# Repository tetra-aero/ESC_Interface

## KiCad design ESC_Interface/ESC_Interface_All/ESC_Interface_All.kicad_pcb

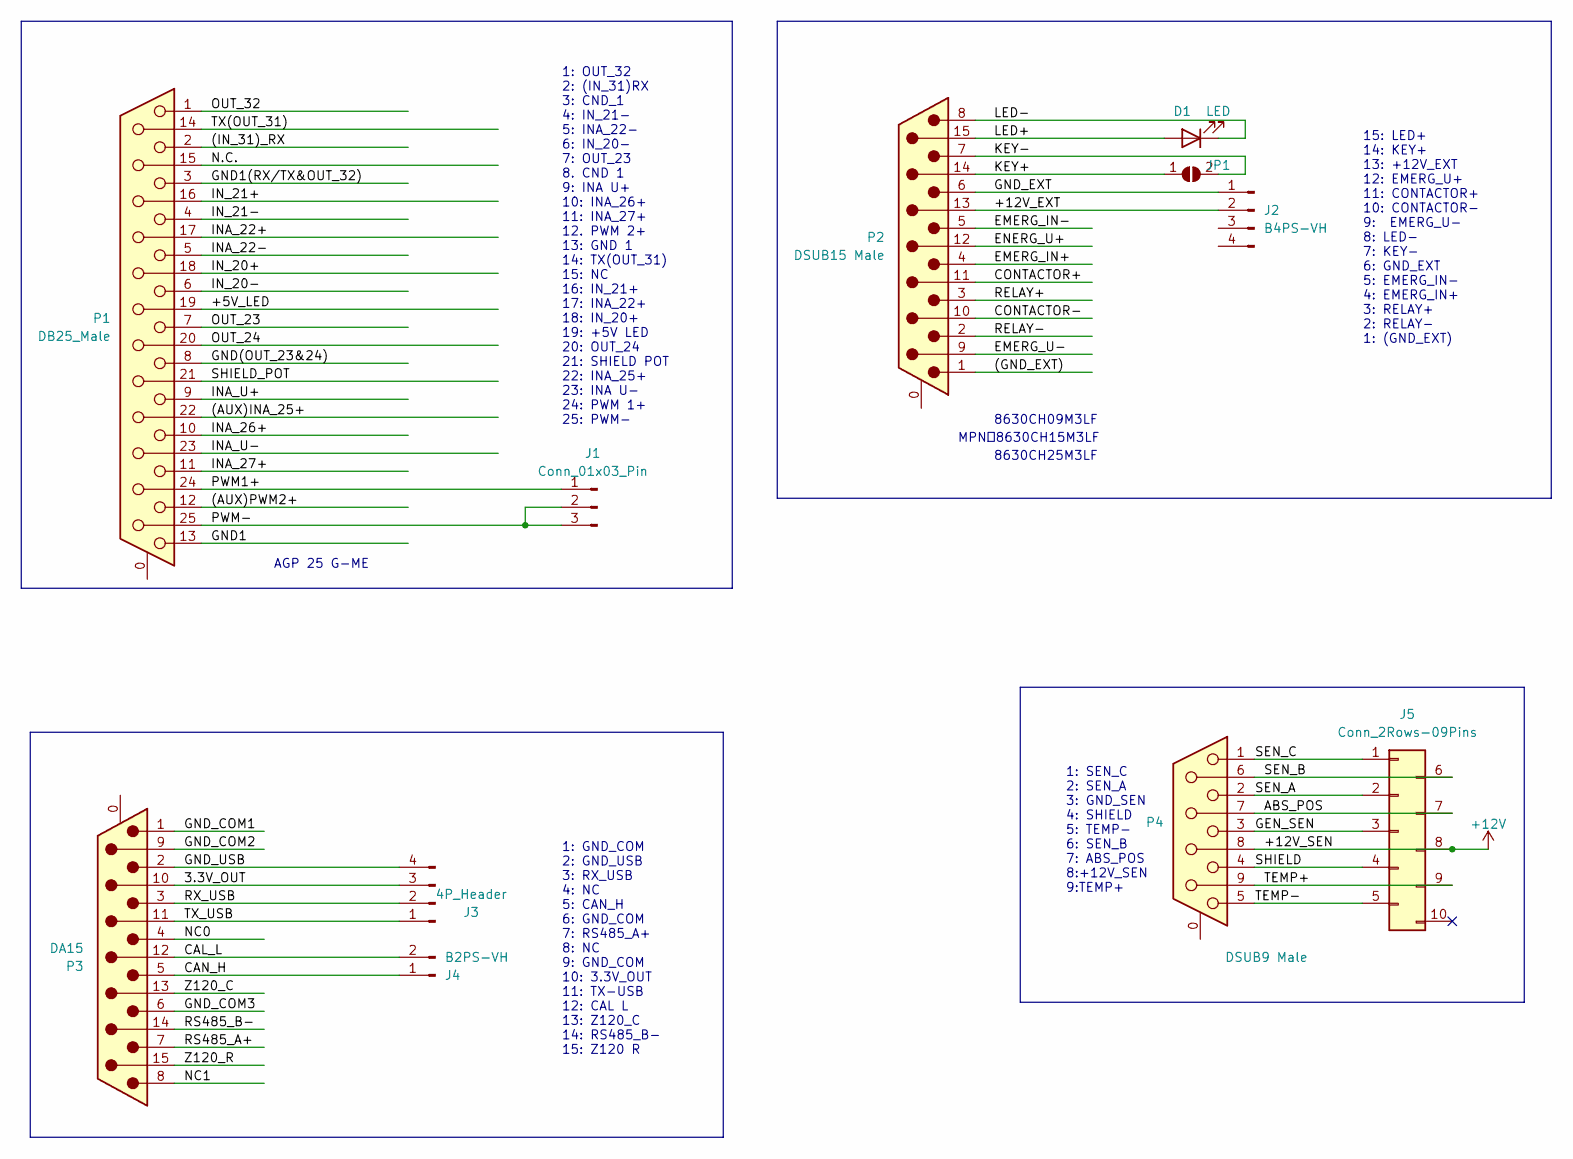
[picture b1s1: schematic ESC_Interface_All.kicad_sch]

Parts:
D1: LED; LED_0603_1608Metric
J1: Conn_01x03_Pin; JST_VH_B3PS-VH_1x03_P3.96mm_Horizontal
J2: B4PS-VH; JST_VH_B4PS-VH_1x04_P3.96mm_Horizontal
J3: 4P_Header; PinHeader_1x04_P2.54mm_Vertical
J4: B2PS-VH; JST_VH_B2PS-VH_1x02_P3.96mm_Horizontal
J5: Conn_2Rows-09Pins; PinSocket_2x05_P2.54mm_Row
JP1: SolderJumper_2_Open; SolderJumper-2_P1.3mm_Open_TrianglePad1.0x1.5mm
P1: DB25_Male; DSUB-25_Male_EdgeMount_P2.77mm_1; MPN DB25P064HTXLF
P2: DSUB15 Male; DSUB-15_Male_EdgeMount_P2.77mm_1; MPN DA15S065HTLF
P3: DA15; DSUB-15_Male_EdgeMount_P2.77mm_1
P4: DSUB9 Male; DSUB-9_Male_Calendar_P2.77x2.84mm_MountingHoles3.1mm_24.99; MPN DE09P065HTXLF

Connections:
+12V: J5.8, P4.8
/3.3V_OUT: J3.3, P3.10
/(AUX)INA_25+: P1.22
/(AUX)PWM2+: P1.12
/(GND_EXT): P2.1
/(IN_31)_RX: P1.2
/+5V_LED: P1.19
/+12V_EXT: J2.2, P2.13
/ABS_POS: J5.7, P4.7
/CAL_L: J4.2, P3.12
/CAN_H: J4.1, P3.5
/CONTACTOR+: P2.11 (P111)
/CONTACTOR-: P2.10
/EMERG_IN+: P2.4
/EMERG_IN-: P2.5
/EMERG_U-: P2.9
/ENERG_U+: P2.12
/GEN_SEN: J5.3, P4.3
/GND1: P1.13
/GND1(RX/TX&OUT_32): P1.3
/GND(OUT_23&24): P1.8
/GND_COM1: P3.1
/GND_COM2: P3.9
/GND_COM3: P3.6
/GND_EXT: J2.1, P2.6
/GND_USB: J3.4, P3.2
/INA_22+: P1.17
/INA_22-: P1.5
/INA_26+: P1.10
/INA_27+: P1.11
/INA_U+: P1.9
/INA_U-: P1.23
/IN_20+: P1.18
/IN_20-: P1.6
/IN_21+: P1.16
/IN_21-: P1.4
/KEY+: JP1.1 (A), P2.14
/KEY-: JP1.2 (B), P2.7
/LED+: D1.2 (A), P2.15
/LED-: D1.1 (K), P2.8
/N.C.: P1.15
/NC0: P3.4
/NC1: P3.8
/OUT_23: P1.7
/OUT_24: P1.20
/OUT_32: P1.1
/PWM1+: J1.1, P1.24
/PWM-: J1.2, J1.3, P1.25
/RELAY+: P2.3
/RELAY-: P2.2
/RS485_A+: P3.7
/RS485_B-: P3.14
/RX_USB: J3.2, P3.3
/SEN_A: J5.2, P4.2
/SEN_B: J5.6, P4.6
/SEN_C: J5.1, P4.1
/SHIELD: J5.4, P4.4
/SHIELD_POT: P1.21
/TEMP+: J5.9, P4.9
/TEMP-: J5.5, P4.5
/TX(OUT_31): P1.14
/TX_USB: J3.1, P3.11 (P111)
/Z120_C: P3.13
/Z120_R: P3.15

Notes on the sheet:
MPN：8630CH15M3LF
8630CH25M3LF
1: OUT_32 2: (IN_31)RX 3: CND_1 4: IN_21- 5: INA_22- 6: IN_20- 7: OUT_23 8. CND 1 9: INA U+ 10: INA_26+ 11: INA_27+ 12. PWM 2+ 13: GND 1 14: TX(OUT_31) 15: NC 16: IN_21+ 17: INA_22+ 18: IN_20+ 19: +5V LED 20: OUT_24 21: SHIELD POT 22: INA_25+ 23: INA U- 24: PWM 1+ 25: PWM-
15: LED+ 14: KEY+ 13: +12V_EXT 12: EMERG_U+ 11: CONTACTOR+ 10: CONTACTOR- 9: EMERG_U- 8: LED- 7: KEY- 6: GND_EXT 5: EMERG_IN- 4: EMERG_IN+ 3: RELAY+ 2: RELAY- 1: (GND_EXT)
1: SEN_C 2: SEN_A 3: GND_SEN 4: SHIELD 5: TEMP- 6: SEN_B 7: ABS_POS 8:+12V_SEN 9:TEMP+
AGP 25 G-ME
8630CH09M3LF
1: GND_COM 2: GND_USB 3: RX_USB 4: NC 5: CAN_H 6: GND_COM 7: RS485_A+ 8: NC 9: GND_COM 10: 3.3V_OUT 11: TX-USB 12: CAL L 13: Z120_C 14: RS485_B- 15: Z120 R

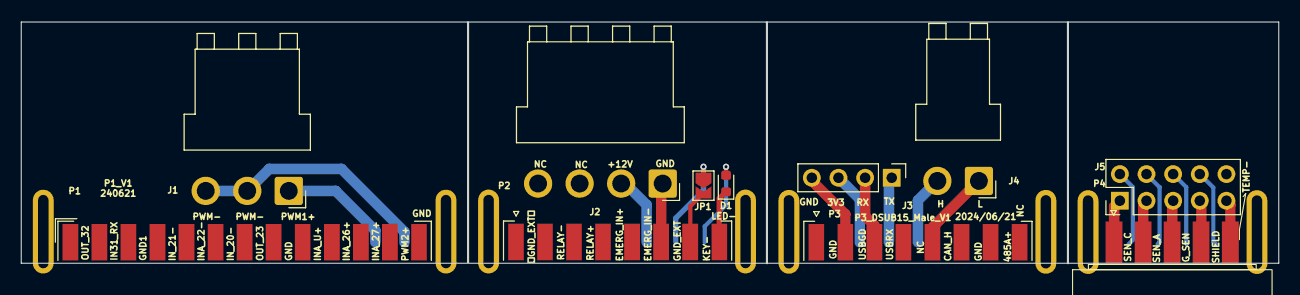
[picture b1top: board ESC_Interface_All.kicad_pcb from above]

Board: 2 copper layers, 119.8 x 23.0 mm, 11 parts (0 on the bottom side), 23 nets.

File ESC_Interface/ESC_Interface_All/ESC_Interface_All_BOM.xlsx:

Ite | Qty | Reference | Value | Description | Datasheet | Footprint | Link | MPN
1 | 1 | D1 | LED |  | ~ | LED_SMD:LED_0603_1608Metric
2 | 1 | J1 | B3PS-VH | Connector Header Through Hole, Right Angle 3 position 0.156" (3.96mm) | https://www.jst-mfg.com/product/pdf/eng/eVH.pdf | Connector_JST:JST_VH_B3PS-VH_1x03_P3.96mm_Horizontal | https://www.digikey.jp/en/products/detail/jst-sales-america-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 | B3PS-VH
3 | 1 | J2 | B4PS-VH | Connector Header Through Hole, Right Angle 4 position 0.156" (3.96mm) | https://www.jst-mfg.com/product/pdf/eng/eVH.pdf | Connector_JST:JST_VH_B4PS-VH_1x04_P3.96mm_Horizontal | https://www.digikey.jp/en/products/detail/jst-sales-america-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 | B4PS-VH
4 | 1 | J4 | B2PS-VH | Connector Header Through Hole, Right Angle 2 position 0.156" (3.96mm) | https://www.jst-mfg.com/product/pdf/eng/eVH.pdf | Connector_JST:JST_VH_B2PS-VH_1x02_P3.96mm_Horizontal | https://www.digikey.jp/en/products/detail/jst-sales-america-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 | B2PS-VH
5 | 1 | P1 | DB25_Male | CONN D-SUB PLUG 25POS SLDR CUP | https://cdn.amphenol-cs.com/media/wysiwyg/files/documentatio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 | Connector_Dsub:DSUB-25_Male_EdgeMount_P2.77mm_1 | https://www.digikey.jp/en/products/detail/amphenol-cs-fci/DB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 | DB25P064HTXLF
6 | 1 | P2 | DSUB15 Male | CONN D-SUB RCPT 15POS SLDR CUP | https://cdn.amphenol-cs.com/media/wysiwyg/files/documentatio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 | Connector_Dsub:DSUB-15_Male_EdgeMount_P2.77mm_1 | https://www.digikey.jp/en/products/detail/amphenol-icc-fci/D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 | DA15S065HTLF
7 | 1 | P3 | DSUB15 Female | CONN D-SUB RCPT 15POS SLDR CUP | https://www.amphenol-cs.com/media/wysiwyg/files/drawing/c-ds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 | 15 Position D-Sub Plug, Male Pins Connector | https://www.digikey.jp/en/products/detail/amphenol-cs-fci/DA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 | DA15P064HTXLF
8 | 1 | P4 | DSUB9 Male | 9 Position D-Sub Plug, Male Pins Connector | https://cdn.amphenol-cs.com/media/wysiwyg/files/documentatio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 | Connector_Dsub:DSUB-9_Male_Calendar_P2.77x2.84mm_MountingHoles3.1mm_24.99 | https://www.digikey.jp/en/products/detail/amphenol-icc-fci/d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 | DE09P065HTXLF

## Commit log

2024-06-25 add ignore
    add ignore
2024-07-02 move pegasus sensor interface and add license
    move pegasus sensor interface and add license
2024-07-17 Fixed P3 material error
